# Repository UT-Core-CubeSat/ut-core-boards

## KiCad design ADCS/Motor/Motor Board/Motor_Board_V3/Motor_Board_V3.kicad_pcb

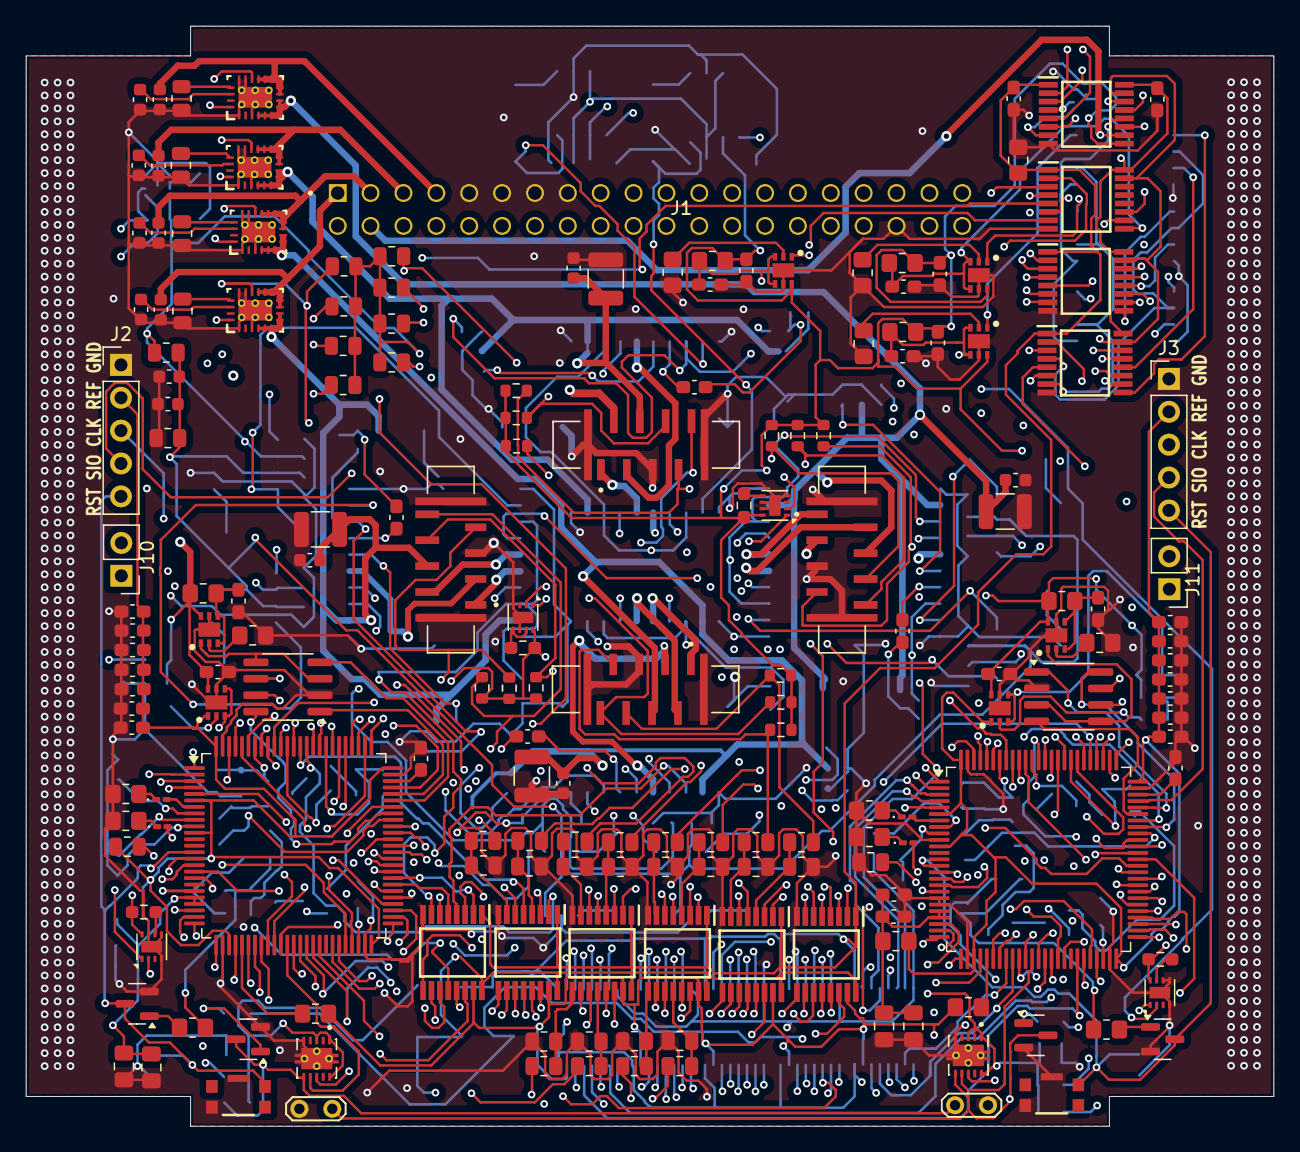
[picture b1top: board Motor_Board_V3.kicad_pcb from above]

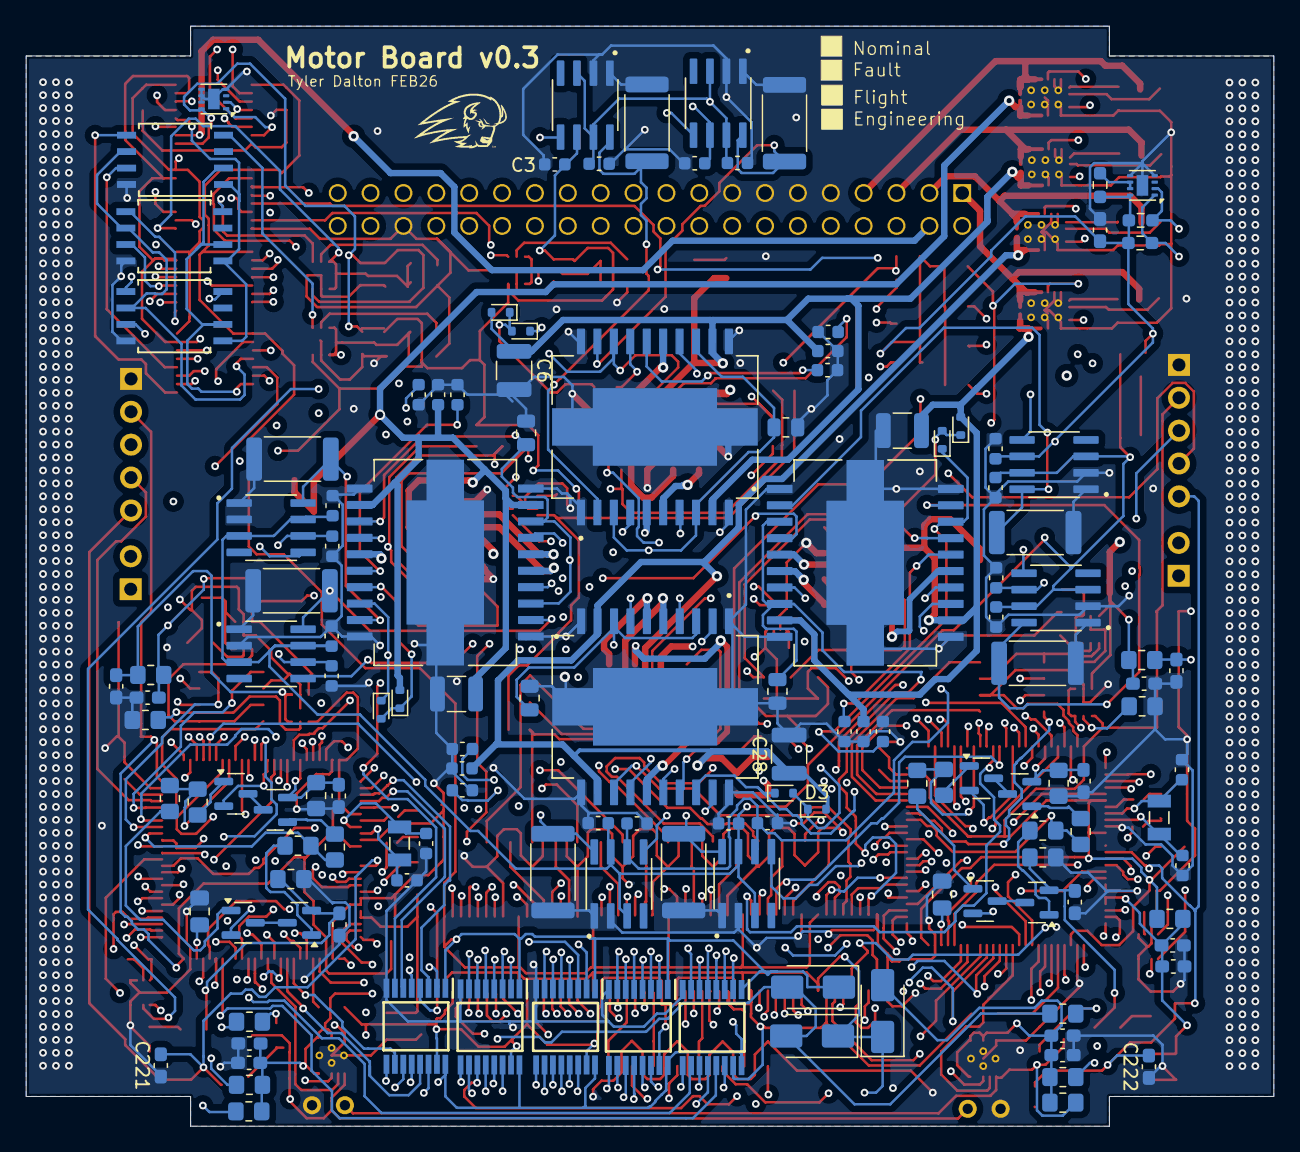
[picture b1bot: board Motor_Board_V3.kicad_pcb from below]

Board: 6 copper layers, 96.4 x 85.0 mm, 320 parts (136 on the bottom side), 345 nets.

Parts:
C1, C10, C12, C21, C23, C32, C35, C44, C136: 1uF; C_0603_1608Metric
C1_RETRY1, C1_RETRY2, C2_RETRY1, C2_RETRY2, C5_RETRY1, C6_RETRY1, C7_RETRY1, C45, C46, C47, C48, C49, C50, C51, C52, C53, C54, C56, C57, C58, C63, C64, C65, C69, C70, C71, C72, C77, C78, C79, C80, C81, C82, C83, C84, C91, C92, C151, C152, C153, C154, C221, C222: 0.1uF; C_0603_1608Metric_Pad1.08x0.95mm_HandSolder
C2, C13, C24, C34: 0.22uF; C_0603_1608Metric
C3, C4, C5, C7, C8, C14, C15, C16, C18, C19, C25, C26, C27, C29, C30, C36, C37, C38, C40, C41, C134, C227, C228, C229, C230: 100nF; C_0603_1608Metric
C6, C17, C28, C39, C231, C232, C233, C234: 47uF; C_1210_3225Metric
C9, C20, C31, C42: 10nF; C_0603_1608Metric_Pad1.08x0.95mm_HandSolder
C11, C22, C33, C43: 10nF; C_0603_1608Metric
C55, C62: 1uF; C_0603_1608Metric_Pad1.08x0.95mm_HandSolder
C59, C66: 10uF; C_0603_1608Metric_Pad1.08x0.95mm_HandSolder
C60, C67: 0.1uF; C_0805_2012Metric_Pad1.18x1.45mm_HandSolder
C61, C68: 1uF; C_0805_2012Metric_Pad1.18x1.45mm_HandSolder
C73, C74: 4.7uF; C_0805_2012Metric_Pad1.18x1.45mm_HandSolder
C223, C224, C225, C226: 15pF; C_0603_1608Metric
D1, D2, D3, D4, D14, D15, D16, D17: 1N4148; D_SOD-523
D6, D7, D9, D10: LED; LED_0201_0603Metric_Pad0.64x0.40mm_HandSolder
D11, D12, D13: SS14; D_SMA
FB1, FB2: FerriteBead_Small; R_0805_2012Metric_Pad1.20x1.40mm_HandSolder
IC1, IC2, IC3, IC4: L6234PD013TR; SOIC127P1420X360-21N
IC5, IC6, IC7, IC8, IC9, IC10, IC11: TPS2552DRVT-1
IC12, IC13, IC14, IC15, IC16, IC17, IC18, IC19, IC20, IC21, IC22, IC23, IC24, IC25, IC26: TMUX1574PWR
J1: IPS1-120-01-L-D-RA
J2, J3: SWD; PinHeader_1x05_P2.54mm_Vertical
J10, J11: Conn_01x02_Pin; PinHeader_1x02_P2.54mm_Vertical
JP10, JP11: WD_Disable; TestPoint_2Pads_Pitch2.54mm_Drill0.8mm
J_Motor1, J_Motor2, J_Motor3, J_Motor4: Conn_02x04_Top_Bottom; AMPHENOL_SFW8S-2STME1LF
Q1, Q2, Q11, Q12: MMBTA94; SOT-23
Q3, Q4, Q5, Q13, Q14, Q15, Q51, Q52: MMBT2222A; SOT-23
R1, R5, R7, R8: 100kR; R_0805_2012Metric
R1_FAULT1, R1_FAULT2, R2_FAULT1, R2_FAULT2, R5_FAULT1, R6_FAULT1, R7_FAULT1: 102kR; R_0805_2012Metric_Pad1.20x1.40mm_HandSolder
R1_ILIM1, R1_ILIM2, R2_ILIM1, R2_ILIM2: 88.7kR; R_0805_2012Metric_Pad1.20x1.40mm_HandSolder
R2, R9, R10, R13, R24, R39, R40, R41, R42, R43, R45, R46, R47, R48, R49, R50, R51, R52, R58, R114, R121, R122, R228, R229: 10kR; R_0805_2012Metric
R3, R4, R6, R15, R16, R17, R34, R35, R36, R53, R54, R55: 4700R; R_0603_1608Metric
R5_ILIM1, R6_ILIM1, R7_ILIM1: 226kR; R_0805_2012Metric_Pad1.20x1.40mm_HandSolder
R11, R12, R18, R19, R37, R38, R56, R57: 15mR; R_2512_6332Metric
R14, R26, R44, R59: 22.1kR; R_0805_2012Metric
R20, R21, R22, R23, R25, R27, R28, R29, R30, R31, R32, R33: 27kR; R_0805_2012Metric
R60, R61: 1kR; R_0805_2012Metric_Pad1.20x1.40mm_HandSolder
R63, R64, R66, R67: 470R; R_0805_2012Metric_Pad1.20x1.40mm_HandSolder
R68, R69, R70, R71, R72, R73, R74: 5kR; R_0603_1608Metric_Pad0.98x0.95mm_HandSolder
R75, R82, R100: 100kR; R_0805_2012Metric_Pad1.20x1.40mm_HandSolder
R76, R77, R78, R79, R94, R95, R96, R97: 10kR; R_0805_2012Metric_Pad1.20x1.40mm_HandSolder
R80, R81, R98, R99: 5kR; R_0805_2012Metric_Pad1.20x1.40mm_HandSolder
R102, R103, R104, R106: 16.5k; R_0805_2012Metric_Pad1.20x1.40mm_HandSolder
R105, R108: 102k; R_0805_2012Metric_Pad1.20x1.40mm_HandSolder
S1, S2: KMR221GLFS; SW_KMR221GLFS
U1, U4, U7, U10: TPS25940ARVCR; RVC0020A
U2, U3, U5, U6, U8, U9, U11, U12: INA240A2QDRQ1; SOIC127P599X175-8N
U13, U14: TCAN330; SOIC-8_3.9x4.9mm_P1.27mm
U15, U16: STM32U5A5VJTx; LQFP-100_14x14mm_P0.5mm
U17, U18, U19: CY15B104QN-50SXI
U20, U21, U22, U23, U24, U25: TMP1075DSG; WSON-8-1EP_2x2mm_P0.5mm_EP0.9x1.6mm
U51, U52: TPS3430WQDRCRQ1; SON50P300X300X100-11N
Y1, Y2: ABS07AIG-32.768KHZ-9-1-T; XTAL_ABS07AIG-32.768KHZ-9-1-T

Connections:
/MUX_3V3: C3.2, C4.1, C14.1, C15.2, C25.1, C26.1, C36.2, C37.1, C77.1, C78.1, C80.1, C81.1, IC9.6 (IN), IC10.6 (IN), IC11.6 (IN), IC12.9 (D3), R1.1, R2.1, R3.2, R4.1, R5.1, R5_FAULT1.2, R6.2, R6_FAULT1.2, R7.1, R7_FAULT1.2, R8.1, R9.1, R10.1, R15.2, R16.2, R17.2, R34.2, R35.2, R36.2, R53.2, R54.2, R55.2, R68.1, R69.1, R70.2, R71.2, R72.2, R73.2, R74.2, R114.1, R121.1, U2.6 (VS), U3.6 (VS), U5.6 (VS), U6.6 (VS), U8.6 (VS), U9.6 (VS), U11.6 (VS), U12.6 (VS), U20.8 (V+), U21.8 (V+), U22.8 (V+), U23.8 (V+), U24.8 (V+), U25.8 (V+)
/Motor1_12v: C5.1, C6.1, C227.1, C231.1, D1.2 (A), IC1.9 (VS_1), IC1.12 (VS_2), J_Motor1.4 (Pin_8), U1.4 (OUT), U1.5 (OUT), U1.6 (OUT), U1.7 (OUT), U1.8 (OUT)
/Motor2_12v: C16.1, C17.1, C228.1, C232.1, D2.2 (A), IC2.9 (VS_1), IC2.12 (VS_2), J_Motor2.4 (Pin_8), U4.4 (OUT), U4.5 (OUT), U4.6 (OUT), U4.7 (OUT), U4.8 (OUT)
/Motor3_12v: C27.1, C28.1, C229.1, C233.1, D3.2 (A), IC3.9 (VS_1), IC3.12 (VS_2), J_Motor3.4 (Pin_8), U7.4 (OUT), U7.5 (OUT), U7.6 (OUT), U7.7 (OUT), U7.8 (OUT)
/Motor4_12v: C38.1, C39.1, C230.1, C234.1, D4.2 (A), IC4.9 (VS_1), IC4.12 (VS_2), J_Motor4.4 (Pin_8), U10.4 (OUT), U10.5 (OUT), U10.6 (OUT), U10.7 (OUT), U10.8 (OUT)
/Motor_1_VCC: C1.1, J1.05, U1.9 (IN), U1.10 (IN), U1.11 (IN), U1.12 (IN), U1.13 (IN)
/Motor_2_VCC: C12.1, J1.07, U4.9 (IN), U4.10 (IN), U4.11 (IN), U4.12 (IN), U4.13 (IN)
/Motor_3_VCC: C23.1, J1.03, U7.9 (IN), U7.10 (IN), U7.11 (IN), U7.12 (IN), U7.13 (IN)
/Motor_4_VCC: C35.1, J1.01, U10.9 (IN), U10.10 (IN), U10.11 (IN), U10.12 (IN), U10.13 (IN)
/mux/MCU block/CANH: J1.40, U13.7 (CANH), U14.7 (CANH)
/mux/MCU block/CANL: J1.38, U13.6 (CANL), U14.6 (CANL)
/mux/MCU block/CS1: IC13.9 (D3), U18.1 (*CS)
/mux/MCU block/CS2: IC14.7 (D2), U19.1 (*CS)
/mux/MCU block/CS3: IC14.9 (D3), U17.1 (*CS)
/mux/MCU block/FRAM1_F: C5_RETRY1.1, IC10.3 (~FAULT), IC10.4 (EN), IC15.4 (D1), R5_FAULT1.1
/mux/MCU block/FRAM2_F: C6_RETRY1.1, IC11.3 (~FAULT), IC11.4 (EN), IC15.7 (D2), R6_FAULT1.1
/mux/MCU block/FRAM3_F: C7_RETRY1.1, IC9.3 (~FAULT), IC9.4 (EN), IC15.9 (D3), R7_FAULT1.1
/mux/MCU block/IC_I2C_SCL: IC12.4 (D1), R68.2, U20.2 (SCL), U21.2 (SCL), U22.2 (SCL), U23.2 (SCL), U24.2 (SCL), U25.2 (SCL)
/mux/MCU block/IC_I2C_SDA: IC12.7 (D2), R69.2, U20.1 (SDA), U21.1 (SDA), U22.1 (SDA), U23.1 (SDA), U24.1 (SDA), U25.1 (SDA)
/mux/MCU block/IC_SCK: IC13.7 (D2), U17.6 (SCK), U18.6 (SCK), U19.6 (SCK)
/mux/MCU block/IC_SI: IC12.12 (D4), U17.5 (SI), U18.5 (SI), U19.5 (SI)
/mux/MCU block/IC_SO: IC13.4 (D1), U17.2 (SO), U18.2 (SO), U19.2 (SO)
/mux/MCU block/MCU1 LED2: D6.2 (A), U15.62 (PD15)
/mux/MCU block/MCU1_3V3: C45.1, C71.1, C151.2, C152.1, D11.2 (A), IC5.6 (IN), IC7.6 (IN), IC12.11 (S3A), J1.02, R1_FAULT1.1, R2_FAULT1.2, R102.2, R106.1, R108.2, U51.1 (VDD1), U51.3 (SET0), U51.10 (VDD2)
/mux/MCU block/MCU1_B0: Q1.2 (E), U15.89 (PB3)
/mux/MCU block/MCU1_CS1: IC13.11 (S3A), U15.47 (PB10)
/mux/MCU block/MCU1_CS2: IC14.5 (S2A), U15.95 (PB8)
/mux/MCU block/MCU1_CS3: IC14.11 (S3A), U15.69 (PA10)
/mux/MCU block/MCU1_FRAM1_F: IC15.2 (S1A), U15.29 (PA4)
/mux/MCU block/MCU1_FRAM2_F: IC15.5 (S2A), U15.24 (PA1)
/mux/MCU block/MCU1_FRAM3_F: IC15.11 (S3A), U15.23 (PA0)
/mux/MCU block/MCU1_I2C1_SCL: IC12.2 (S1A), U15.92 (PB6)
/mux/MCU block/MCU1_I2C1_SDA: IC12.5 (S2A), U15.93 (PB7)
/mux/MCU block/MCU1_M1_En: IC20.2 (S1A), U15.66 (PC9)
/mux/MCU block/MCU1_M1_Fault: IC18.11 (S3A), U15.97 (PE0)
/mux/MCU block/MCU1_M1_HallA: IC16.2 (S1A), U15.81 (PD0)
/mux/MCU block/MCU1_M1_HallB: IC16.5 (S2A), U15.82 (PD1)
/mux/MCU block/MCU1_M1_HallC: IC17.2 (S1A), U15.84 (PD3)
/mux/MCU block/MCU1_M1_IA: IC20.11 (S3A), U15.15 (PC0)
/mux/MCU block/MCU1_M1_IB: IC20.14 (S4A), U15.16 (PC1)
/mux/MCU block/MCU1_M1_Kill: IC22.2 (S1A), U15.3 (PE4)
/mux/MCU block/MCU1_M1_pwmA: IC24.2 (S1A), U15.59 (PD12)
/mux/MCU block/MCU1_M1_pwmB: IC24.5 (S2A), U15.60 (PD13)
/mux/MCU block/MCU1_M1_pwmC: IC25.2 (S1A), U15.61 (PD14)
/mux/MCU block/MCU1_M2_En: IC20.5 (S2A), U15.80 (PC12)
/mux/MCU block/MCU1_M2_Fault: IC18.14 (S4A), U15.98 (PE1)
/mux/MCU block/MCU1_M2_HallA: IC17.5 (S2A), U15.85 (PD4)
/mux/MCU block/MCU1_M2_HallB: IC18.2 (S1A), U15.86 (PD5)
/mux/MCU block/MCU1_M2_HallC: IC18.5 (S2A), U15.87 (PD6)
/mux/MCU block/MCU1_M2_IA: IC21.11 (S3A), U15.17 (PC2)
/mux/MCU block/MCU1_M2_IB: IC21.14 (S4A), U15.18 (PC3)
/mux/MCU block/MCU1_M2_Kill: IC22.5 (S2A), U15.4 (PE5)
/mux/MCU block/MCU1_M2_pwmA: IC25.5 (S2A), U15.90 (PB4)
/mux/MCU block/MCU1_M2_pwmB: IC26.2 (S1A), U15.36 (PB1)
/mux/MCU block/MCU1_M2_pwmC: IC26.5 (S2A), U15.35 (PB0)
/mux/MCU block/MCU1_M3_En: IC21.2 (S1A), U15.58 (PD11)
/mux/MCU block/MCU1_M3_Fault: IC19.11 (S3A), U15.1 (PE2)
/mux/MCU block/MCU1_M3_HallA: IC19.2 (S1A), U15.88 (PD7)
/mux/MCU block/MCU1_M3_HallB: IC19.5 (S2A), U15.55 (PD8)
/mux/MCU block/MCU1_M3_HallC: IC16.11 (S3A), U15.56 (PD9)
/mux/MCU block/MCU1_M3_IA: IC22.11 (S3A), U15.33 (PC4)
/mux/MCU block/MCU1_M3_IB: IC22.14 (S4A), U15.34 (PC5)
/mux/MCU block/MCU1_M3_Kill: IC23.2 (S1A), U15.5 (PE6)
/mux/MCU block/MCU1_M3_pwmA: IC24.11 (S3A), U15.65 (PC8)
/mux/MCU block/MCU1_M3_pwmB: IC24.14 (S4A), U15.64 (PC7)
/mux/MCU block/MCU1_M3_pwmC: IC25.11 (S3A), U15.63 (PC6)
/mux/MCU block/MCU1_M4_En: IC21.5 (S2A), U15.57 (PD10)
/mux/MCU block/MCU1_M4_Fault: IC19.14 (S4A), U15.2 (PE3)
/mux/MCU block/MCU1_M4_HallA: IC16.14 (S4A), U15.39 (PE8)
/mux/MCU block/MCU1_M4_HallB: IC17.11 (S3A), U15.40 (PE9)
/mux/MCU block/MCU1_M4_HallC: IC17.14 (S4A), U15.41 (PE10)
/mux/MCU block/MCU1_M4_IA: IC23.11 (S3A), U15.31 (PA6)
/mux/MCU block/MCU1_M4_IB: IC23.14 (S4A), U15.32 (PA7)
/mux/MCU block/MCU1_M4_Kill: IC23.5 (S2A), U15.38 (PE7)
/mux/MCU block/MCU1_M4_pwmA: IC25.14 (S4A), U15.44 (PE13)
/mux/MCU block/MCU1_M4_pwmB: IC26.11 (S3A), U15.45 (PE14)
/mux/MCU block/MCU1_M4_pwmC: IC26.14 (S4A), U15.42 (PE11)
/mux/MCU block/MCU1_SPI2_MISO: IC13.2 (S1A), U15.53 (PB14)
/mux/MCU block/MCU1_SPI2_MOSI: IC12.14 (S4A), U15.54 (PB15)
/mux/MCU block/MCU1_SPI2_SCK: IC13.5 (S2A), U15.52 (PB13)
/mux/MCU block/MCU1_WD: U15.37 (PB2), U51.7 (WDI)
/mux/MCU block/MCU1_WP1: IC13.14 (S4A), U15.51 (PB12)
/mux/MCU block/MCU1_WP2: IC14.2 (S1A), U15.96 (PB9)
/mux/MCU block/MCU1_WP3: IC14.14 (S4A), U15.91 (PB5)
/mux/MCU block/MCU2 LED 2: D9.2 (A), U16.62 (PD15)
/mux/MCU block/MCU2_3V3: C46.1, C72.1, C153.2, C154.1, D12.2 (A), D13.2 (A), IC6.6 (IN), IC8.6 (IN), IC12.10 (S3B), J1.04, R1_FAULT2.1, R2_FAULT2.2, R103.1, R104.2, R105.2, U52.1 (VDD1), U52.3 (SET0), U52.10 (VDD2)
/mux/MCU block/MCU2_B0: Q11.2 (E), U16.89 (PB3)
/mux/MCU block/MCU2_CS1: IC13.10 (S3B), U16.47 (PB10)
/mux/MCU block/MCU2_CS2: IC14.6 (S2B), U16.95 (PB8)
/mux/MCU block/MCU2_CS3: IC14.10 (S3B), U16.69 (PA10)
/mux/MCU block/MCU2_FRAM1_F: IC15.3 (S1B), U16.29 (PA4)
/mux/MCU block/MCU2_FRAM2_F: IC15.6 (S2B), U16.24 (PA1)
/mux/MCU block/MCU2_FRAM3_F: IC15.10 (S3B), U16.23 (PA0)
/mux/MCU block/MCU2_I2C1_SCL: IC12.3 (S1B), U16.92 (PB6)
/mux/MCU block/MCU2_I2C1_SDA: IC12.6 (S2B), U16.93 (PB7)
/mux/MCU block/MCU2_M1_En: IC20.3 (S1B), U16.66 (PC9)
/mux/MCU block/MCU2_M1_Fault: IC18.10 (S3B), U16.97 (PE0)
/mux/MCU block/MCU2_M1_HallA: IC16.3 (S1B), U16.81 (PD0)
/mux/MCU block/MCU2_M1_HallB: IC16.6 (S2B), U16.82 (PD1)
/mux/MCU block/MCU2_M1_HallC: IC17.3 (S1B), U16.84 (PD3)
/mux/MCU block/MCU2_M1_IA: IC20.10 (S3B), U16.15 (PC0)
/mux/MCU block/MCU2_M1_IB: IC20.13 (S4B), U16.16 (PC1)
/mux/MCU block/MCU2_M1_Kill: IC22.3 (S1B), U16.3 (PE4)
/mux/MCU block/MCU2_M1_pwmA: IC24.3 (S1B), U16.59 (PD12)
/mux/MCU block/MCU2_M1_pwmB: IC24.6 (S2B), U16.60 (PD13)
/mux/MCU block/MCU2_M1_pwmC: IC25.3 (S1B), U16.61 (PD14)
/mux/MCU block/MCU2_M2_En: IC20.6 (S2B), U16.80 (PC12)
/mux/MCU block/MCU2_M2_Fault: IC18.13 (S4B), U16.98 (PE1)
/mux/MCU block/MCU2_M2_HallA: IC17.6 (S2B), U16.85 (PD4)
/mux/MCU block/MCU2_M2_HallB: IC18.3 (S1B), U16.86 (PD5)
/mux/MCU block/MCU2_M2_HallC: IC18.6 (S2B), U16.87 (PD6)
/mux/MCU block/MCU2_M2_IA: IC21.10 (S3B), U16.17 (PC2)
/mux/MCU block/MCU2_M2_IB: IC21.13 (S4B), U16.18 (PC3)
/mux/MCU block/MCU2_M2_Kill: IC22.6 (S2B), U16.4 (PE5)
/mux/MCU block/MCU2_M2_pwmA: IC25.6 (S2B), U16.90 (PB4)
/mux/MCU block/MCU2_M2_pwmB: IC26.3 (S1B), U16.36 (PB1)
/mux/MCU block/MCU2_M2_pwmC: IC26.6 (S2B), U16.35 (PB0)
/mux/MCU block/MCU2_M3_En: IC21.3 (S1B), U16.58 (PD11)
/mux/MCU block/MCU2_M3_Fault: IC19.10 (S3B), U16.1 (PE2)
/mux/MCU block/MCU2_M3_HallA: IC19.3 (S1B), U16.88 (PD7)
/mux/MCU block/MCU2_M3_HallB: IC19.6 (S2B), U16.55 (PD8)
/mux/MCU block/MCU2_M3_HallC: IC16.10 (S3B), U16.56 (PD9)
/mux/MCU block/MCU2_M3_IA: IC22.10 (S3B), U16.33 (PC4)
/mux/MCU block/MCU2_M3_IB: IC22.13 (S4B), U16.34 (PC5)
/mux/MCU block/MCU2_M3_Kill: IC23.3 (S1B), U16.5 (PE6)
/mux/MCU block/MCU2_M3_pwmA: IC24.10 (S3B), U16.65 (PC8)
/mux/MCU block/MCU2_M3_pwmB: IC24.13 (S4B), U16.64 (PC7)
/mux/MCU block/MCU2_M3_pwmC: IC25.10 (S3B), U16.63 (PC6)
/mux/MCU block/MCU2_M4_En: IC21.6 (S2B), U16.57 (PD10)
/mux/MCU block/MCU2_M4_Fault: IC19.13 (S4B), U16.2 (PE3)
/mux/MCU block/MCU2_M4_HallA: IC16.13 (S4B), U16.39 (PE8)
/mux/MCU block/MCU2_M4_HallB: IC17.10 (S3B), U16.40 (PE9)
/mux/MCU block/MCU2_M4_HallC: IC17.13 (S4B), U16.41 (PE10)
/mux/MCU block/MCU2_M4_IA: IC23.10 (S3B), U16.31 (PA6)
/mux/MCU block/MCU2_M4_IB: IC23.13 (S4B), U16.32 (PA7)
/mux/MCU block/MCU2_M4_Kill: IC23.6 (S2B), U16.38 (PE7)
/mux/MCU block/MCU2_M4_pwmA: IC25.13 (S4B), U16.44 (PE13)
/mux/MCU block/MCU2_M4_pwmB: IC26.10 (S3B), U16.45 (PE14)
/mux/MCU block/MCU2_M4_pwmC: IC26.13 (S4B), U16.42 (PE11)
/mux/MCU block/MCU2_SPI2_MISO: IC13.3 (S1B), U16.53 (PB14)
/mux/MCU block/MCU2_SPI2_MOSI: IC12.13 (S4B), U16.54 (PB15)
/mux/MCU block/MCU2_SPI2_SCK: IC13.6 (S2B), U16.52 (PB13)
/mux/MCU block/MCU2_WD: U16.37 (PB2), U52.7 (WDI)
/mux/MCU block/MCU2_WP1: IC13.13 (S4B), U16.51 (PB12)
/mux/MCU block/MCU2_WP2: IC14.3 (S1B), U16.96 (PB9)
/mux/MCU block/MCU2_WP3: IC14.13 (S4B), U16.91 (PB5)
/mux/MCU block/NRST1: C222.2, J2.5, Q5.3 (C), S1.4, U15.14 (NRST)
/mux/MCU block/NRST2: C221.2, J3.5, Q15.3 (C), S2.4, U16.14 (NRST)
/mux/MCU block/PA6_1: R78.2, R79.2, U15.67 (PA8)
/mux/MCU block/PA6_2: R96.2, R97.2, U16.67 (PA8)
/mux/MCU block/PA7_1: Q2.2 (E), U15.77 (PA15)
/mux/MCU block/PA7_2: Q12.2 (E), U16.77 (PA15)
/mux/MCU block/PA9_1: U13.8 (S), U15.68 (PA9)
/mux/MCU block/PA9_2: U14.8 (S), U16.68 (PA9)
/mux/MCU block/PA11_1: U13.4 (RXD), U15.70 (PA11)
/mux/MCU block/PA11_2: U14.4 (RXD), U16.70 (PA11)
/mux/MCU block/PA12_1: U13.1 (TXD), U15.71 (PA12)
/mux/MCU block/PA12_2: U14.1 (TXD), U16.71 (PA12)
/mux/MCU block/PA13_1: J2.4, U15.72 (PA13)
/mux/MCU block/PA13_2: J3.4, U16.72 (PA13)
/mux/MCU block/PA14_1: J2.3, U15.76 (PA14)
/mux/MCU block/PA14_2: J3.3, U16.76 (PA14)
/mux/MCU block/PD2_1: R76.1, R77.1, U15.83 (PD2)
/mux/MCU block/PD2_2: R94.1, R95.1, U16.83 (PD2)
/mux/MCU block/PH3_1: C83.1, Q3.2 (E), R80.1, U15.94 (PH3)
/mux/MCU block/PH3_2: C91.1, Q13.2 (E), R98.1, U16.94 (PH3)
/mux/MCU block/USART2_1: U15.25 (PA2), U16.26 (PA3)
/mux/MCU block/USART2_2: U15.26 (PA3), U16.25 (PA2)
/mux/MCU block/VREF1: C48.2, C49.2, C50.2, C56.2, C57.2, C58.2, C59.2, FB1.2, IC5.1 (OUT), J2.2, R228.2, U15.6 (VBAT), U15.11 (VDD), U15.28 (VDD), U15.50 (VDD), U15.75 (VDD), U15.100 (VDD)
/mux/MCU block/VREF2: C52.2, C53.2, C54.2, C63.2, C64.2, C65.2, C66.2, FB2.2, IC6.1 (OUT), J3.2, U16.6 (VBAT), U16.11 (VDD), U16.28 (VDD), U16.50 (VDD), U16.75 (VDD), U16.100 (VDD)
/mux/MCU block/WP1: IC13.12 (D4), U18.3 (*WP)
/mux/MCU block/WP2: IC14.4 (D1), U19.3 (*WP)
/mux/MCU block/WP3: IC14.12 (D4), U17.3 (*WP)
/mux/MCU_MR: IC12.15 (~EN), IC13.15 (~EN), IC14.15 (~EN), IC15.15 (~EN), IC16.15 (~EN), IC17.15 (~EN), IC18.15 (~EN), IC19.15 (~EN), IC20.15 (~EN), IC21.15 (~EN), IC22.15 (~EN), IC23.15 (~EN), IC24.15 (~EN), IC25.15 (~EN), IC26.15 (~EN), R60.2, R61.2
/mux/MUX_SEL: C82.2, D13.1 (K), IC12.1 (SEL), IC13.1 (SEL), IC14.1 (SEL), IC15.1 (SEL), IC16.1 (SEL), IC17.1 (SEL), IC18.1 (SEL), IC19.1 (SEL), IC20.1 (SEL), IC21.1 (SEL), IC22.1 (SEL), IC23.1 (SEL), IC24.1 (SEL), IC25.1 (SEL), IC26.1 (SEL), R75.2
/mux/Motor1_En: IC1.3 (EN2), IC1.8 (EN1), IC1.13 (EN3), IC20.7 (D2), R13.2
/mux/Motor1_Fault: IC18.9 (D3), R9.2, U1.20 (FLT_N)
/mux/Motor1_Hall_A: IC16.4 (D1), R20.1, R42.2
/mux/Motor1_Hall_B: IC16.7 (D2), R21.1, R41.2
/mux/Motor1_Hall_C: IC17.4 (D1), R22.1, R40.2
/mux/Motor1_IA: IC20.9 (D3), U2.5 (OUT)
/mux/Motor1_IB: IC20.12 (D4), U3.5 (OUT)
/mux/Motor1_Kill: IC22.4 (D1), R7.2, U1.14 (EN_UVLO)
/mux/Motor1_pwmA: IC1.7 (IN1), IC24.4 (D1)
/mux/Motor1_pwmB: IC1.4 (IN2), IC24.7 (D2)
/mux/Motor1_pwmC: IC1.14 (IN3), IC25.4 (D1)
/mux/Motor2_En: IC2.3 (EN2), IC2.8 (EN1), IC2.13 (EN3), IC20.4 (D1), R24.2
/mux/Motor2_Fault: IC18.12 (D4), R2.2, U4.20 (FLT_N)
/mux/Motor2_Hall_A: IC17.7 (D2), R23.1, R39.2
/mux/Motor2_Hall_B: IC18.4 (D1), R25.1, R48.2
/mux/Motor2_Hall_C: IC18.7 (D2), R27.1, R47.2
/mux/Motor2_IA: IC21.9 (D3), U5.5 (OUT)
/mux/Motor2_IB: IC21.12 (D4), U6.5 (OUT)
/mux/Motor2_Kill: IC22.7 (D2), R5.2, U4.14 (EN_UVLO)
/mux/Motor2_pwmA: IC2.7 (IN1), IC25.7 (D2)
/mux/Motor2_pwmB: IC2.4 (IN2), IC26.4 (D1)
/mux/Motor2_pwmC: IC2.14 (IN3), IC26.7 (D2)
/mux/Motor3_En: IC3.3 (EN2), IC3.8 (EN1), IC3.13 (EN3), IC21.4 (D1), R43.2
/mux/Motor3_Fault: IC19.9 (D3), R10.2, U7.20 (FLT_N)
/mux/Motor3_Hall_A: IC19.4 (D1), R28.1, R46.2
/mux/Motor3_Hall_B: IC19.7 (D2), R29.1, R45.2
/mux/Motor3_Hall_C: IC16.9 (D3), R30.1, R52.2
/mux/Motor3_IA: IC22.9 (D3), U8.5 (OUT)
/mux/Motor3_IB: IC22.12 (D4), U9.5 (OUT)
/mux/Motor3_Kill: IC23.4 (D1), R8.2, U7.14 (EN_UVLO)
/mux/Motor3_pwmA: IC3.7 (IN1), IC24.9 (D3)
/mux/Motor3_pwmB: IC3.4 (IN2), IC24.12 (D4)
/mux/Motor3_pwmC: IC3.14 (IN3), IC25.9 (D3)
/mux/Motor4_En: IC4.3 (EN2), IC4.8 (EN1), IC4.13 (EN3), IC21.7 (D2), R58.2
/mux/Motor4_Fault: IC19.12 (D4), R114.2, U10.20 (FLT_N)
/mux/Motor4_Hall_A: IC16.12 (D4), R31.1, R51.2
/mux/Motor4_Hall_B: IC17.9 (D3), R32.1, R50.2
/mux/Motor4_Hall_C: IC17.12 (D4), R33.1, R49.2
/mux/Motor4_IA: IC23.9 (D3), U11.5 (OUT)
/mux/Motor4_IB: IC23.12 (D4), U12.5 (OUT)
/mux/Motor4_Kill: IC23.7 (D2), R1.2, U10.14 (EN_UVLO)
/mux/Motor4_pwmA: IC4.7 (IN1), IC25.12 (D4)
/mux/Motor4_pwmB: IC4.4 (IN2), IC26.9 (D3)
/mux/Motor4_pwmC: IC4.14 (IN3), IC26.12 (D4)
/mux/VCC_MUX: C79.2, D11.1 (K), D12.1 (K), IC12.16 (VDD), IC13.16 (VDD), IC14.16 (VDD), IC15.16 (VDD), IC16.16 (VDD), IC17.16 (VDD), IC18.16 (VDD), IC19.16 (VDD), IC20.16 (VDD), IC21.16 (VDD), IC22.16 (VDD), IC23.16 (VDD), IC24.16 (VDD), IC25.16 (VDD), IC26.16 (VDD)
GND: C1.2, C1_RETRY1.2, C1_RETRY2.2, C2.2, C2_RETRY1.2, C2_RETRY2.2, C3.1, C4.2, C5.2, C5_RETRY1.2, C6.2, C6_RETRY1.2, C7.1, C7_RETRY1.2, C8.1, C10.2, C11.2, C12.2, C13.2, C14.2, C15.1, C16.2, C17.2, C18.1, C19.1, C21.2, C22.2, C23.2, C24.2, C25.2, C26.2, C27.2, C28.2, C29.1, C30.1, C32.2, C33.2, C34.2, C35.2, C36.1, C37.2, C38.2, C39.2, C40.1, C41.1, C43.2, C44.2, C45.2, C46.2, C47.1, C48.1, C49.1, C50.1, C51.1, C52.1, C53.1, C54.1, C55.1, C56.1, C57.1, C58.1, C59.1, C60.2, C61.2, C62.1, C63.1, C64.1, C65.1, C66.1, C67.2, C68.2, C69.1, C70.1, C71.2, C72.2, C73.2, C74.2, C77.2, C78.2, C79.1, C80.2, C81.2, C82.1, C83.2, C84.2, C91.2, C92.2, C134.2, C136.2, C151.1, C152.2, C153.1, C154.2, C221.1, C222.1, C223.1, C224.2, C225.1, C226.2, C227.2, C228.2, C229.2, C230.2, C231.2, C232.2, C233.2, C234.2, IC1.1 (GND_1), IC1.10 (GND_2), IC1.11 (GND_3), IC1.20 (GND_4), IC1.21 (EP), IC1.22 (EP), IC1.23 (EP), IC2.1 (GND_1), IC2.10 (GND_2), IC2.11 (GND_3), IC2.20 (GND_4), IC2.21 (EP), IC2.22 (EP), IC2.23 (EP), IC3.1 (GND_1), IC3.10 (GND_2), IC3.11 (GND_3), IC3.20 (GND_4), IC3.21 (EP), IC3.22 (EP), IC3.23 (EP), IC4.1 (GND_1), IC4.10 (GND_2), IC4.11 (GND_3), IC4.20 (GND_4), IC4.21 (EP), IC4.22 (EP), IC4.23 (EP), IC5.5 (GND), IC5.7 (EP), IC6.5 (GND), IC6.7 (EP), IC7.5 (GND), IC7.7 (EP), IC8.5 (GND), IC8.7 (EP), IC9.5 (GND), IC9.7 (EP), IC10.5 (GND), IC10.7 (EP), IC11.5 (GND), IC11.7 (EP), IC12.8 (GND), IC13.8 (GND), IC14.8 (GND), IC15.8 (GND), IC16.8 (GND), IC17.8 (GND), IC18.8 (GND), IC19.8 (GND), IC20.8 (GND), IC21.8 (GND), IC22.8 (GND), IC23.8 (GND), IC24.8 (GND), IC25.8 (GND), IC26.8 (GND), J1.09, J1.11, J1.13, J1.15, J1.36, J2.1, J3.1, JP10.2 (B), JP11.2 (B), J_Motor1.5 (Pin_4), J_Motor1.SH1, J_Motor1.SH2, J_Motor2.5 (Pin_4), J_Motor2.SH1, J_Motor2.SH2, J_Motor3.5 (Pin_4), J_Motor3.SH1, J_Motor3.SH2, J_Motor4.5 (Pin_4), J_Motor4.SH1, J_Motor4.SH2, Q5.2 (E), Q15.2 (E), Q51.2 (E), Q52.2 (E), R1_ILIM1.2, R1_ILIM2.2, R2_ILIM1.2, R2_ILIM2.2, R5_ILIM1.2, R6_ILIM1.2, R7_ILIM1.2, R11.2, R12.2, R13.1, R14.2, R18.2, R19.2, R24.1, R26.2, R37.2, R38.2, R39.1, R40.1, R41.1, R42.1, R43.1, R44.2, R45.1, R46.1, R47.1, R48.1, R49.1, R50.1, R51.1, R52.1, R56.2, R57.2, R58.1, R59.2, R63.2, R64.2, R66.2, R67.2, R75.1, R80.2, R81.2, R98.2, R99.2, R122.1, R229.2, S1.2, S1.5, S2.2, S2.5, U1.1 (DEVSLP), U1.3 (PGTH), U1.15 (OVP), U1.16 (GND), U1.21 (PAD), U2.1 (IN-), U2.2 (GND), U3.1 (IN-), U3.2 (GND), U4.1 (DEVSLP), U4.3 (PGTH), U4.15 (OVP), U4.16 (GND), U4.21 (PAD), U5.1 (IN-), U5.2 (GND), U6.1 (IN-), U6.2 (GND), U7.1 (DEVSLP), U7.3 (PGTH), U7.15 (OVP), U7.16 (GND), U7.21 (PAD), U8.1 (IN-), U8.2 (GND), U9.1 (IN-), U9.2 (GND), U10.1 (DEVSLP), U10.3 (PGTH), U10.15 (OVP), U10.16 (GND), U10.21 (PAD), U11.1 (IN-), U11.2 (GND), U12.1 (IN-), U12.2 (GND), U13.2 (GND), U14.2 (GND), U15.10 (VSS), U15.19 (VSSA), U15.20 (VREF-), U15.27 (VSS), U15.49 (VSS), U15.74 (VSS), U15.99 (VSS), U16.10 (VSS), U16.19 (VSSA), U16.20 (VREF-), U16.27 (VSS), U16.49 (VSS), U16.74 (VSS), U16.99 (VSS), U17.4 (VSS), U18.4 (VSS), U19.4 (VSS), U20.4 (GND), U20.5 (A2), U20.6 (A1), U20.7 (A0), U20.9 (EP), U21.4 (GND), U21.5 (A2), U21.6 (A1), U21.9 (EP), U22.4 (GND), U22.5 (A2), U22.7 (A0), U22.9 (EP), U23.4 (GND), U23.5 (A2), U23.9 (EP), U24.4 (GND), U24.6 (A1), U24.7 (A0), U24.9 (EP), U25.4 (GND), U25.6 (A1), U25.9 (EP), U51.5 (GND), U51.11 (EPAD), U52.5 (GND), U52.11 (EPAD)
unnamed: C9.2, D1.1 (K), D14.2 (A)
unnamed: D6.1 (K), R63.1
unnamed: D7.2 (A), U15.7 (PC13)
unnamed: D7.1 (K), R64.1
unnamed: D9.1 (K), R66.1
unnamed: D10.2 (A), U16.7 (PC13)
unnamed: D10.1 (K), R67.1
unnamed: C2.1, D14.1 (K), IC1.18 (VBOOT)
unnamed: C20.2, D2.1 (K), D15.2 (A)
unnamed: C13.1, D15.1 (K), IC2.18 (VBOOT)
unnamed: C31.2, D3.1 (K), D16.2 (A)
unnamed: C24.1, D16.1 (K), IC3.18 (VBOOT)
unnamed: C42.2, D4.1 (K), D17.2 (A)
unnamed: C34.1, D17.1 (K), IC4.18 (VBOOT)
unnamed: IC1.6 (OUT1), J_Motor1.1 (Pin_7)
unnamed: IC1.5 (OUT2), J_Motor1.2 (Pin_6)
unnamed: IC1.15 (OUT3), J_Motor1.3 (Pin_5)
unnamed: IC1.2 (SENSE_1), R12.1, U2.8 (IN+)
unnamed: IC1.19 (SENSE_2), R11.1, U3.8 (IN+)
unnamed: C9.1, IC1.17 (VCP)
unnamed: C10.1, IC1.16 (VREF)
unnamed: IC2.6 (OUT1), J_Motor2.1 (Pin_7)
unnamed: IC2.5 (OUT2), J_Motor2.2 (Pin_6)
unnamed: IC2.15 (OUT3), J_Motor2.3 (Pin_5)
unnamed: IC2.2 (SENSE_1), R19.1, U5.8 (IN+)
unnamed: IC2.19 (SENSE_2), R18.1, U6.8 (IN+)
unnamed: C20.1, IC2.17 (VCP)
unnamed: C21.1, IC2.16 (VREF)
unnamed: IC3.6 (OUT1), J_Motor3.1 (Pin_7)
unnamed: IC3.5 (OUT2), J_Motor3.2 (Pin_6)
unnamed: IC3.15 (OUT3), J_Motor3.3 (Pin_5)
unnamed: IC3.2 (SENSE_1), R38.1, U8.8 (IN+)
unnamed: IC3.19 (SENSE_2), R37.1, U9.8 (IN+)
unnamed: C31.1, IC3.17 (VCP)
unnamed: C32.1, IC3.16 (VREF)
unnamed: IC4.6 (OUT1), J_Motor4.1 (Pin_7)
unnamed: IC4.5 (OUT2), J_Motor4.2 (Pin_6)
unnamed: IC4.15 (OUT3), J_Motor4.3 (Pin_5)
unnamed: IC4.2 (SENSE_1), R57.1, U11.8 (IN+)
unnamed: IC4.19 (SENSE_2), R56.1, U12.8 (IN+)
unnamed: C42.1, IC4.17 (VCP)
unnamed: C44.1, IC4.16 (VREF)
unnamed: C1_RETRY1.1, IC5.3 (~FAULT), IC5.4 (EN), R1_FAULT1.2
unnamed: IC5.2 (ILIM), R1_ILIM1.1
unnamed: C1_RETRY2.1, IC6.3 (~FAULT), IC6.4 (EN), R1_FAULT2.2
unnamed: IC6.2 (ILIM), R1_ILIM2.1
unnamed: C2_RETRY1.1, IC7.3 (~FAULT), IC7.4 (EN), R2_FAULT1.1
unnamed: IC7.2 (ILIM), R2_ILIM1.1
unnamed: IC7.1 (OUT), U13.3 (VCC), U13.5 (SHDN)
unnamed: C2_RETRY2.1, IC8.3 (~FAULT), IC8.4 (EN), R2_FAULT2.1
unnamed: IC8.2 (ILIM), R2_ILIM2.1
unnamed: IC8.1 (OUT), U14.3 (VCC), U14.5 (SHDN)
unnamed: IC9.2 (ILIM), R7_ILIM1.1
unnamed: IC9.1 (OUT), U17.8 (VDD)
unnamed: IC10.2 (ILIM), R5_ILIM1.1
unnamed: IC10.1 (OUT), U18.8 (VDD)
unnamed: IC11.2 (ILIM), R6_ILIM1.1
unnamed: IC11.1 (OUT), U19.8 (VDD)
unnamed: J10.1, U15.79 (PC11)
unnamed: J10.2, U15.78 (PC10)
unnamed: J11.1, U16.79 (PC11)
unnamed: J11.2, U16.78 (PC10)
unnamed: JP10.1 (A), Q52.3 (C), R105.1, U52.6 (SET1)
unnamed: JP11.1 (A), Q51.3 (C), R108.1, U51.6 (SET1)
unnamed: J_Motor1.6 (Pin_1), R4.2, R20.2
unnamed: J_Motor1.7 (Pin_2), R6.1, R21.2
unnamed: J_Motor1.8 (Pin_3), R3.1, R22.2
unnamed: J_Motor2.6 (Pin_1), R15.1, R23.2
unnamed: J_Motor2.7 (Pin_2), R16.1, R25.2
unnamed: J_Motor2.8 (Pin_3), R17.1, R27.2
unnamed: J_Motor3.6 (Pin_1), R28.2, R34.1
unnamed: J_Motor3.7 (Pin_2), R29.2, R35.1
unnamed: J_Motor3.8 (Pin_3), R30.2, R36.1
unnamed: J_Motor4.6 (Pin_1), R31.2, R53.1
unnamed: J_Motor4.7 (Pin_2), R32.2, R54.1
unnamed: J_Motor4.8 (Pin_3), R33.2, R55.1
unnamed: Q1.1 (B), R76.2
unnamed: Q1.3 (C), Q3.3 (C)
unnamed: Q2.1 (B), R77.2
unnamed: Q2.3 (C), Q4.3 (C)
unnamed: Q3.1 (B), R78.1
unnamed: Q4.1 (B), R79.1
unnamed: C84.1, Q4.2 (E), R81.1, R82.1
unnamed: Q5.1 (B), R82.2
unnamed: Q11.1 (B), R94.2
unnamed: Q11.3 (C), Q13.3 (C)
unnamed: Q12.1 (B), R95.2
unnamed: Q12.3 (C), Q14.3 (C)
unnamed: Q13.1 (B), R96.1
unnamed: Q14.1 (B), R97.1
unnamed: C92.1, Q14.2 (E), R99.1, R100.1
unnamed: Q15.1 (B), R100.2
unnamed: Q51.1 (B), R103.2
unnamed: Q52.1 (B), R106.2
unnamed: C11.1, U1.18 (DVDT)
unnamed: R14.1, U1.17 (ILIM)
unnamed: C22.1, U4.18 (DVDT)
unnamed: R26.1, U4.17 (ILIM)
unnamed: C33.1, U7.18 (DVDT)
unnamed: R44.1, U7.17 (ILIM)
unnamed: C43.1, U10.18 (DVDT)
unnamed: R59.1, U10.17 (ILIM)
unnamed: C7.2, C8.2, C18.2, C19.2, C29.2, C30.2, C40.2, C41.2, C134.1, C136.1, R121.2, R122.2, U2.3 (REF2), U2.7 (REF1), U3.3 (REF2), U3.7 (REF1), U5.3 (REF2), U5.7 (REF1), U6.3 (REF2), U6.7 (REF1), U8.3 (REF2), U8.7 (REF1), U9.3 (REF2), U9.7 (REF1), U11.3 (REF2), U11.7 (REF1), U12.3 (REF2), U12.7 (REF1)
unnamed: R60.1, U15.30 (PA5)
unnamed: C223.2, U15.8 (PC14), Y1.1
unnamed: C224.1, U15.9 (PC15), Y1.2
unnamed: R228.1, U15.46 (PE15)
unnamed: C73.1, U15.48 (VCAP)
unnamed: C47.2, C55.2, C60.1, C61.1, FB1.1, U15.21 (VREF+), U15.22 (VDDA)
unnamed: C69.2, U15.73 (VDDUSB)
unnamed: R61.1, U16.30 (PA5)
unnamed: C225.2, U16.8 (PC14), Y2.1
unnamed: C226.1, U16.9 (PC15), Y2.2
unnamed: R229.1, U16.46 (PE15)
unnamed: C74.1, U16.48 (VCAP)
unnamed: C51.2, C62.2, C67.1, C68.1, FB2.1, U16.21 (VREF+), U16.22 (VDDA)
unnamed: C70.2, U16.73 (VDDUSB)
unnamed: R70.1, U21.7 (A0)
unnamed: R71.1, U22.6 (A1)
unnamed: R72.1, U23.6 (A1), U23.7 (A0)
unnamed: R73.1, U24.5 (A2)
unnamed: R74.1, U25.5 (A2), U25.7 (A0)
unnamed: R102.1, U51.8 (*WDO)
unnamed: R104.1, U52.8 (*WDO)
